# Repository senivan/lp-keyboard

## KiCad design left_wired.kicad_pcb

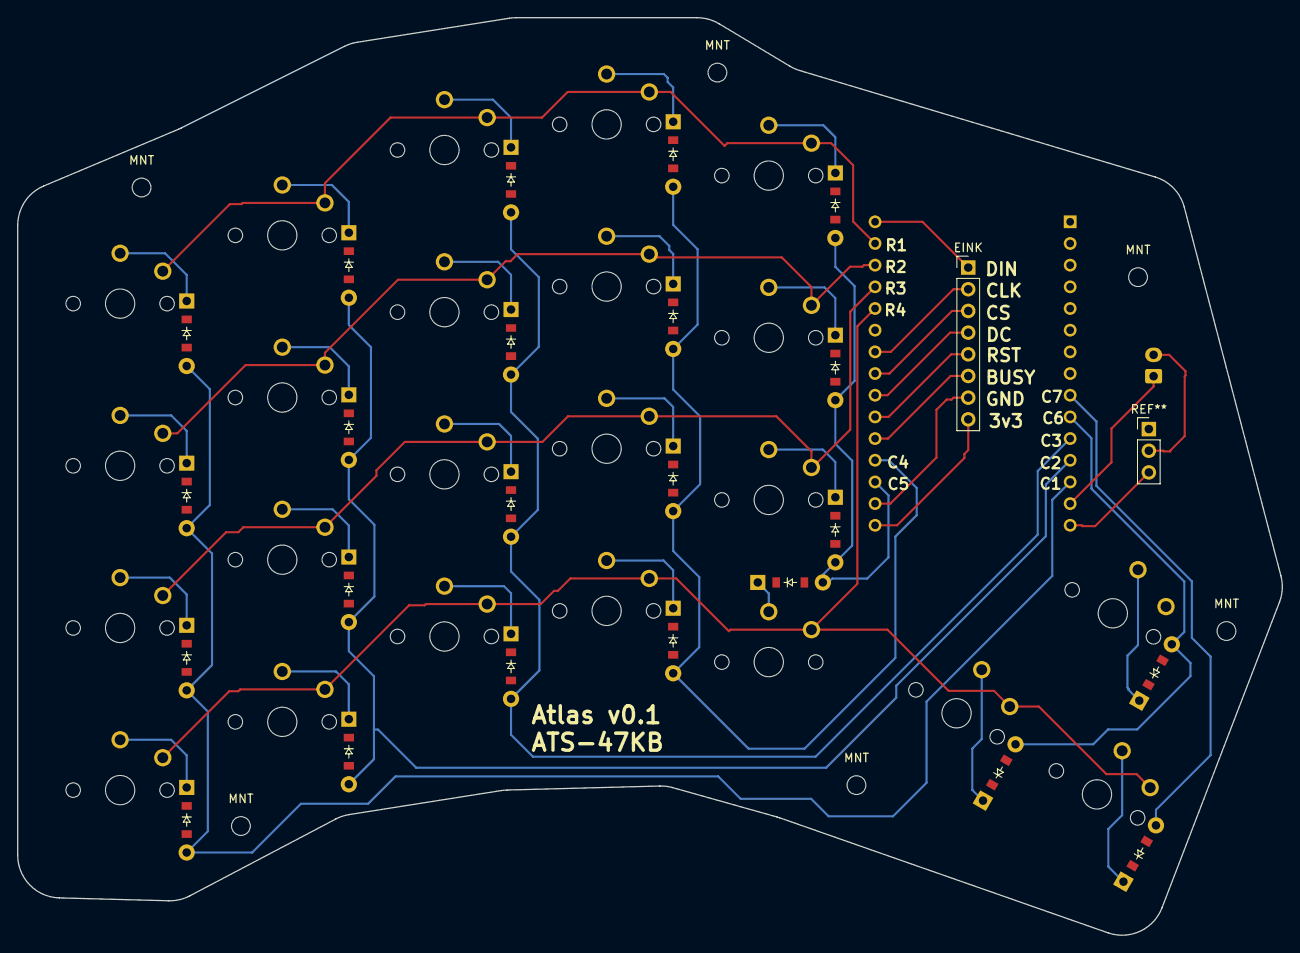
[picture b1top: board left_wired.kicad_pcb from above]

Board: 2 copper layers, 148.2 x 107.5 mm, 54 parts (1 on the bottom side), 23 nets.

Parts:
BAT: JST_EH_B2B-EH-A_1x02_P2.50mm_Vertical
D1, D2, D3, D4, D5, D6, D7, D8, D9, D10, D11, D12, D13, D14, D15, D16, D17, D18, D19, D20, D21, D22, D23: ComboDiode
EINK: PinHeader_1x08_P2.54mm_Vertical
MNT: MountingHole_2.2mm_M2
MNT#2, MNT#3, MNT#4, MNT#5, MNT#6: MountingHole_2.2mm_M2
S1, S2, S3, S4, S5, S6, S7, S8, S9, S10, S11, S12, S13, S14, S15, S16, S17, S18, S19, S20, S21, S22, S23: PG1350

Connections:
fifth_bottom: D18.2, S18.2
fifth_home: D19.2, S19.2
fifth_mods: D17.2, S17.2
fifth_top: D20.2, S20.2
first_bottom: D2.2, S2.2
first_home: D3.2, S3.2
first_mods: D1.2, S1.2
first_top: D4.2, S4.2
fourth_bottom: D14.2, S14.2
fourth_home: D15.2, S15.2
fourth_mods: D13.2, S13.2
fourth_top: D16.2, S16.2
macro_bottom: D21.2, S21.2
pinky_bottom: D22.2, S22.2
ring_bottom: D23.2, S23.2
second_bottom: D6.2, S6.2
second_home: D7.2, S7.2
second_mods: D5.2, S5.2
second_top: D8.2, S8.2
third_bottom: D10.2, S10.2
third_home: D11.2, S11.2
third_mods: D9.2, S9.2
third_top: D12.2, S12.2

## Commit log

2025-01-14 Wired pcbs for row/column scanning
2025-01-14 Updated diod placement
